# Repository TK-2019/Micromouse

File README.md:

# Micromouse
Robotics Club , SNT ,  IITK 

Here one can find the resourses behinf our project along with the assignment ans submissions for the mentees.

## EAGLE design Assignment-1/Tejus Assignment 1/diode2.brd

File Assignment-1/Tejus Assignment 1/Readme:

Here are the answers of assignment 1

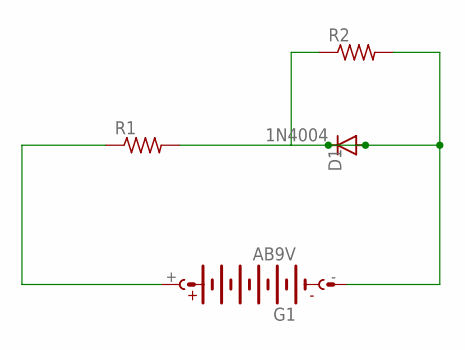
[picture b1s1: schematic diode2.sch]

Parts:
D1: 1N4004; DO41-10
G1: AB9V
R1, R2: R-US_R0805; R0805

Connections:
unnamed: G1.+, R1.1
unnamed: D1.A, D1.C, G1.-, R1.2, R2.1, R2.2

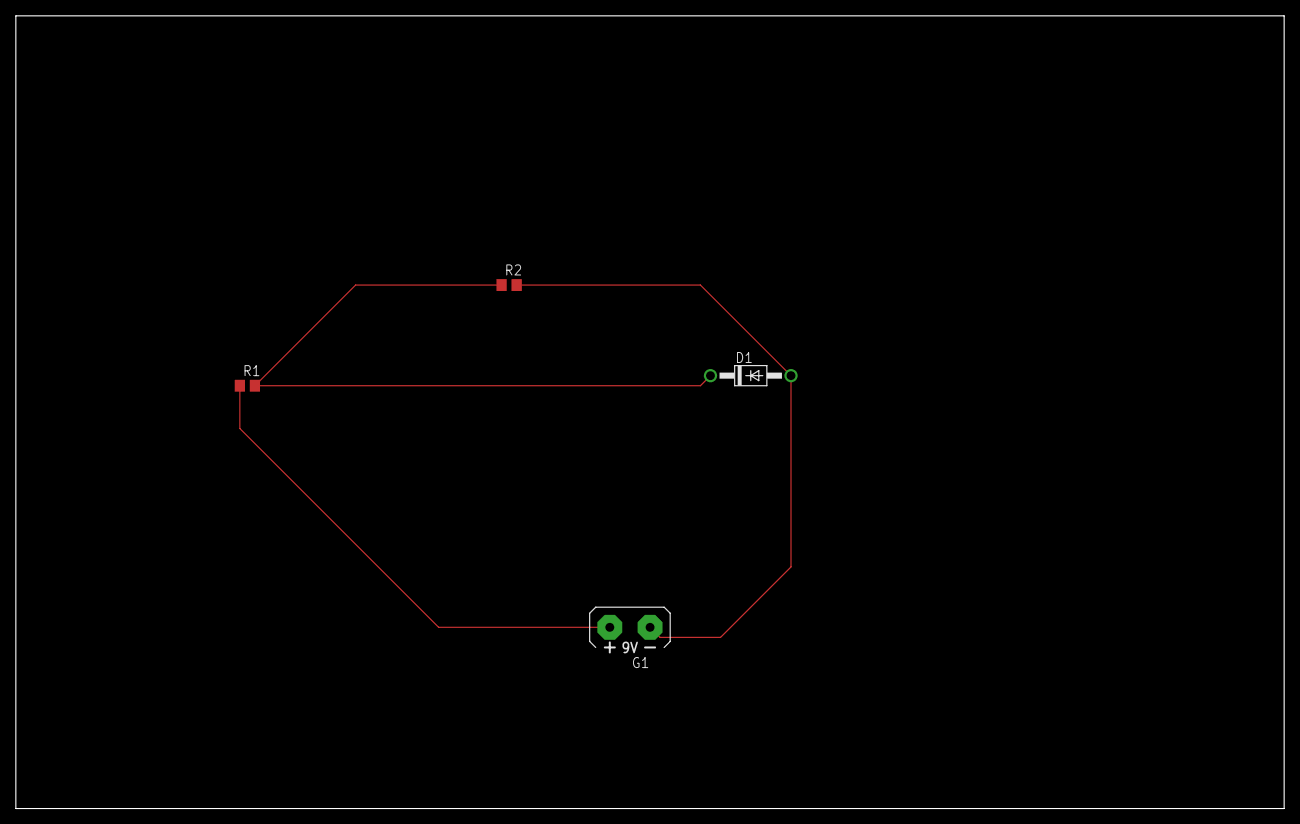
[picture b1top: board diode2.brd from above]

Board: 2 copper layers, 160.0 x 100.0 mm, 4 parts (0 on the bottom side), 2 nets.

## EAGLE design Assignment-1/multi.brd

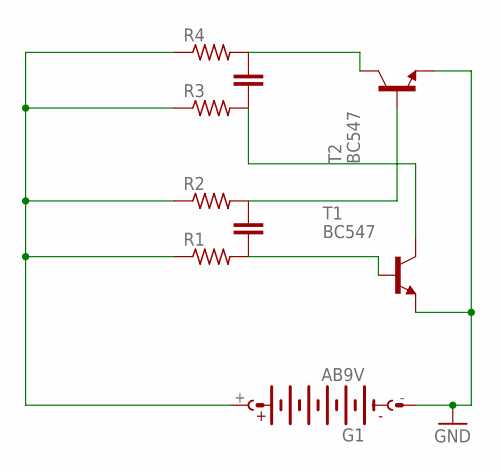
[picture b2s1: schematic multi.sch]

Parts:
G1: AB9V
R1, R2, R3, R4: R-US_R0805; R0805
T1, T2: BC547; TO92

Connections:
GND: G1.-, T1.1 (E), T2.1 (E)
unnamed: G1.+, R1.1, R2.1, R3.1, R4.1
unnamed: R1.2, T1.2 (B)
unnamed: R3.2, T1.3 (C)
unnamed: R2.2, T2.2 (B)
unnamed: R4.2, T2.3 (C)

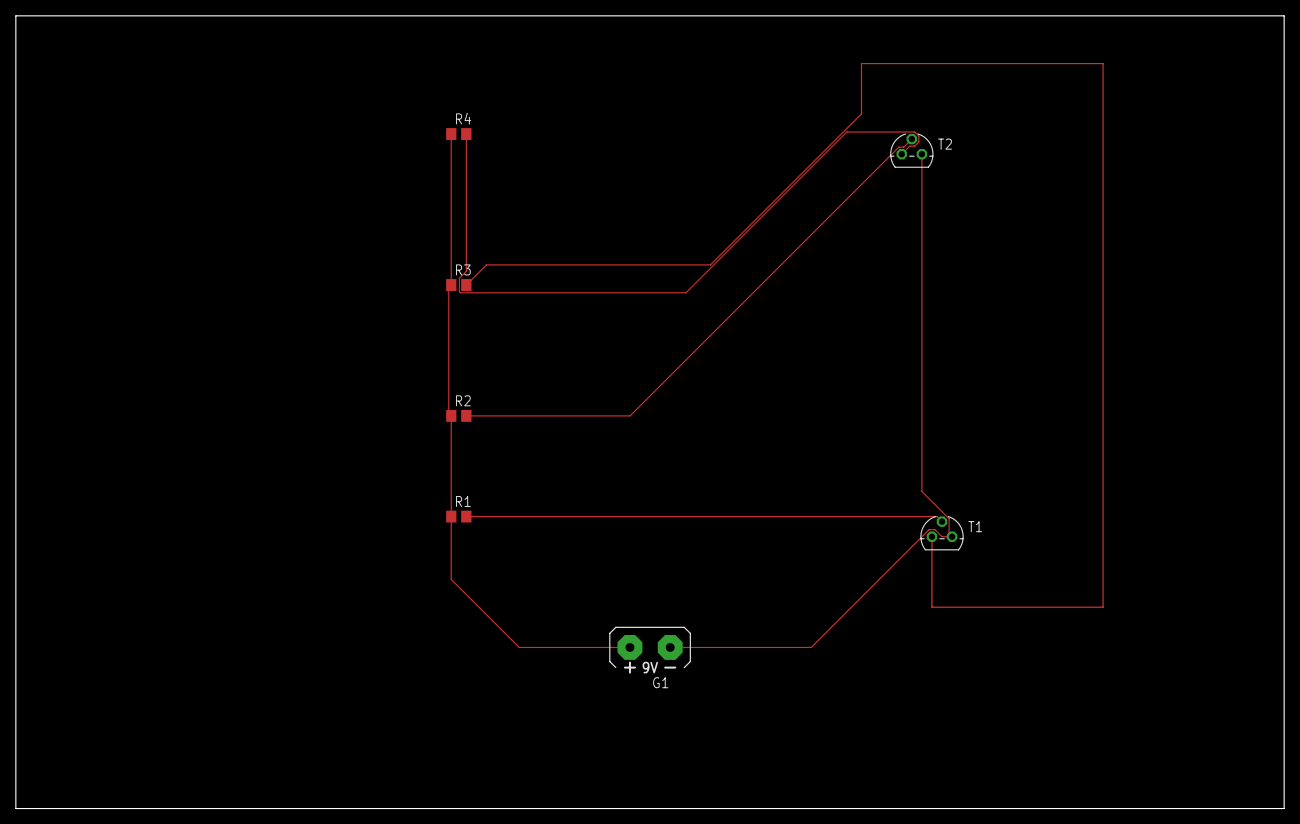
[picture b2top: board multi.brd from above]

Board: 2 copper layers, 160.0 x 100.0 mm, 7 parts (0 on the bottom side), 6 nets.

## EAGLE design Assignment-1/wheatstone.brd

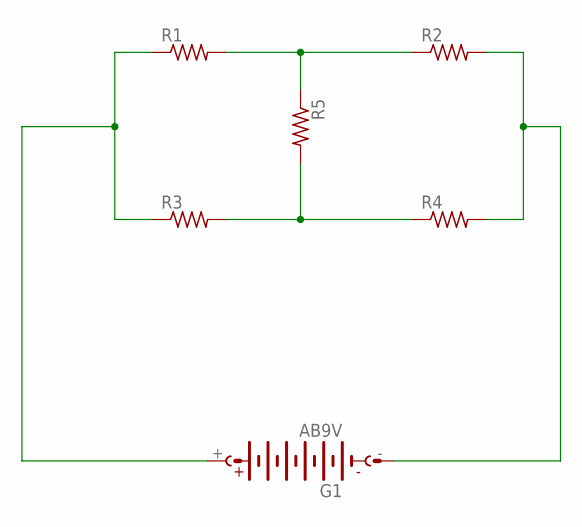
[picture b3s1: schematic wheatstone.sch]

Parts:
G1: AB9V
R1, R2, R3, R4, R5: R-US_R0603; R0603

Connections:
unnamed: G1.+, R1.1, R3.1
unnamed: R1.2, R2.1, R5.1
unnamed: G1.-, R2.2, R4.2
unnamed: R3.2, R4.1, R5.2

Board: 2 copper layers, 6 parts (0 on the bottom side), 4 nets, no tracks yet.

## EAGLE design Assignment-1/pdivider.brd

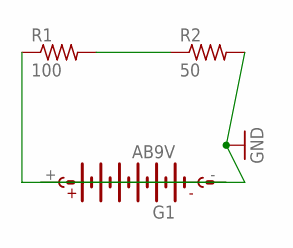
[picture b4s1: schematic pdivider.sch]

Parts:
G1: AB9V
R1: 100; R0603
R2: 50; R0603

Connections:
GND: G1.+, R2.2
unnamed: G1.-, R1.1
unnamed: R1.2, R2.1

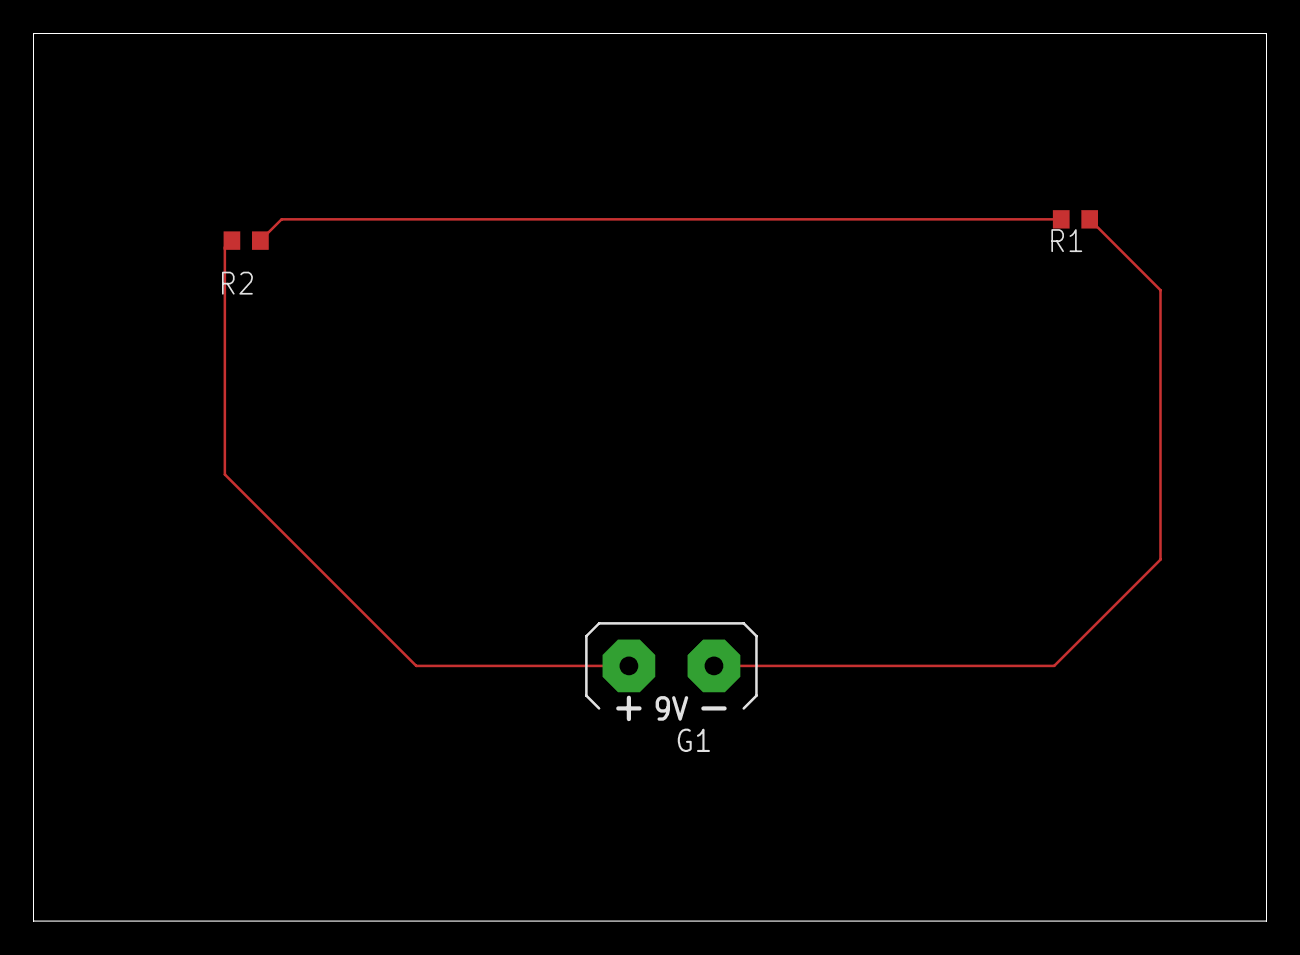
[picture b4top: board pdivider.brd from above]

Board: 2 copper layers, 73.6 x 53.0 mm, 3 parts (0 on the bottom side), 3 nets.

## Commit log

2022-06-23 class 1 of algo
2022-06-24 setting up submissions
2022-06-24 Create Testing
2022-06-24 Assignment-1
2022-06-24 Create Tejus Khandelwal
2022-06-25 class 2 dfs
2022-06-25 demo git desk
2022-06-25 class 2 bfs
2022-06-25 class 2 software
2022-06-26 Create Tejus Assignment 1
